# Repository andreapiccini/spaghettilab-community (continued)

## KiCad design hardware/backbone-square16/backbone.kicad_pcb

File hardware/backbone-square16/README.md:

# Backbone a 16 righe — variante separata

Stato: assegnazione GPIO e circuito a 16 porte applicati e verificati sulla netlist. PCB sincronizzato, disposizione preliminare 68 × 68 mm, non sbrogliato e non pronto per produzione. La Backbone originale non è stata sovrascritta.

Aprire `backbone.kicad_pro`. Il secondo foglio `ports16.kicad_sch` contiene i dieci canali aggiunti e i nuovi comandi. `gpio16-allocation.csv` è la tabella completa; `connectivity-checks.json` riporta le verifiche di collegamento.

## Righe configurabili

| Posizione | Sinistra: GPIO | Destra: GPIO |
|---|---:|---:|
| 1 | 7 | 12 |
| 2 | 8 | 15 |
| 3 | 9 | 16 |
| 4 | 10 | 38 |
| 5 | 1 | 39 |
| 6 | 2 | 40 |
| 7 | 6 | 41 |
| 8 | 11 | 42 |

Sinistra: J18/J19/J21, contatti 1–8, reti PORT_A0–PORT_A7. Destra: J22/J23/J24, contatti 1–8, reti PORT_A8–PORT_A15. Ogni riga ha tre contatti comuni. Le due metà sono indipendenti: nessuna matrice di collegamento fra righe.

Ogni riga dispone di selezione VCORE (3,3 V), GND, GPIO o alta impedenza mediante MOSFET e switch analogico. I GPIO non sono tolleranti a 5 V. Le nuove porte riprendono la topologia delle sei esistenti: shunt 0,1 Ω con prese Kelvin e collegamento 0 Ω rimovibile verso lo stadio di potenza. Il valore dello shunt non costituisce una specifica di corrente o di accuratezza già validata per la futura mezzanina.

L1–L7 hanno ADC1; L8 e R1–R3 hanno ADC2, con le limitazioni del relativo driver/modalità di acquisizione. R4–R8 non hanno ADC diretto. Tutti i 16 segnali restano GPIO reali del micro; gli expander comandano solo le selezioni e i servizi lenti.

## Funzioni conservate

| Funzione | GPIO conservati |
|---|---|
| I²C | 4, 5 |
| CAN | 17, 18 |
| USB | 19, 20 |
| LED RGB | 21 |
| Collegamento SPI e relativi segnali di controllo | 13, 14, 43, 44 |
| UART di programmazione AG32 | 47, 48 |

I GPIO 0, 3, 45 e 46 non sono assegnati alle righe; GPIO35–37 sono esclusi perché riservati alla PSRAM della variante ESP32 prevista. Gli eventuali collegamenti storici di questi segnali sulla vecchia interfaccia mezzanina non li rendono disponibili: andranno trattati come riservati nella revisione del connettore.

Le reti preesistenti dei servizi arrivano ancora ai rispettivi connettori. I comandi prima attestati ai dieci GPIO recuperati ora fanno capo agli expander. Il vecchio firmware non è compatibile con questa variante senza aggiornamento.

## Comandi aggiunti

Tre TCA9535 della famiglia già usata, U32/U33/U34, indirizzi I²C a 7 bit 0x21/0x22/0x23. U25 resta a 0x20. Gli indirizzi 0x20–0x23 devono essere riservati sulla rete I²C condivisa.

- U32: comandi P/N delle porte A6–A13, alternati su P00…P07 e P10…P17.
- U33: P/N delle porte A14–A15, dieci enable degli switch A6–A15 e ESP_ISO4_N/ESP_ISO5_N.
- U34: P00=MEAS_S0, P01=MEAS_S1, P02=MEAS_S2, P03=MEAS_INHIBIT, P04=EXT_SPI_CS_N, P05=ESP_AG_BOOT0, P06=ESP_AG_RESET_N, P07=MEZZ_PRESENT_N (ingresso). P10–P17 sono collegati a GND e devono restare ingressi.

La selezione EXT_SPI_CS_N ora richiede una transazione I²C: utilizzarla ai confini di una transazione SPI, mantenendola attiva durante il trasferimento. Non è più un chip-select commutabile direttamente a ogni parola tramite periferica ESP. Clock e dati del collegamento SPI conservano i GPIO diretti. Boot/reset dell'AG32 restano disponibili con il nuovo comando I²C.

## Contratto firmware da implementare

Gli expander partono come ingressi a freddo. Pull-up dei gate P e degli enable, e pull-down dei gate N, tengono disattivati i dieci nuovi stadi. Il reset del solo ESP32 non resetta gli expander: non garantisce il ritorno automatico in alta impedenza. Le sei porte esistenti conservano anche la loro logica di ownership.

Prima di rendere gli expander uscite, scrivere i latch nello stato sicuro. Per i nuovi componenti:

| Expander | Output port 0 | Output port 1 | Configuration port 0 | Configuration port 1 |
|---|---|---|---|---|
| U32 | 0x55 | 0x55 | 0x00 | 0x00 |
| U33 | 0xF5 | 0xFF | 0x00 | 0x00 |
| U34 | 0x58 | 0x00 | 0x80 | 0xFF |

Per U34 abilitare le uscite soltanto dopo aver assegnato l'ownership dei segnali condivisi: l'AG32 deve lasciare in alta impedenza i pin che l'expander pilota. In assenza di accordo lasciare i bit condivisi come ingressi. I selettori MEAS_S0–S2 hanno pull-down: non possono generare il livello alto con la sola emulazione open-drain. Occorre pilotaggio push-pull con un solo proprietario alla volta. Anche l'accesso I²C da due controllori richiede arbitraggio/ownership nel firmware.

Ogni cambio funzione deve passare da uno stato intermedio spento: disabilitare lo switch GPIO, spegnere entrambi i MOSFET, attendere l'assestamento, quindi abilitare una sola funzione. Non abilitare mai contemporaneamente P e N. Non alimentare una riga mentre ESP/FPGA o un dispositivo esterno la pilotano. Per ricevere/generare un segnale dalla futura mezzanina: P e N spenti, percorso ESP disabilitato, interfaccia esterna compatibile con tensioni e alimentazioni.

Questa tabella è una specifica di inizializzazione, non firmware già compilato o collaudato. Verificare limiti logici e stato di accensione anche con il modello esatto di expander acquistato e con la futura mezzanina collegata.

## Cosa resta per mezzanina e misure

La revisione del connettore è rinviata come concordato. Le sei porte storiche conservano i collegamenti esistenti. I dieci nuovi segnali e le venti nuove prese Kelvin non sono ancora esportati su J10/J11. Non è quindi ancora possibile usare tutte le 16 righe dall'FPGA della mezzanina attuale. Non sono stati aggiunti INA o DAC alla Backbone.

L'alta impedenza degli switch non elimina capacità parassite, leakage o collegamenti dello stadio di potenza: non è una garanzia di banda analogica. I link 0 Ω permettono di scollegare lo stadio di potenza per configurazioni dedicate; la banda va verificata con la mezzanina e il layout definitivo.

## Meccanica e controlli

PCB preliminare 68 × 68 mm, con magnetici ai lati e antenna ESP al bordo superiore. Tre socket per banco, interasse fra copie 5,08 mm, gap centrale 7,62 mm. Gli interassi delle prime sei posizioni fra J17/J18 e J20/J19 restano 33,02 mm. J10/J11 mantengono 24,175 mm tra centri; la posizione assoluta della mezzanina cambia e va verificata sul suo PCB. I nuovi componenti sono sul top; il modulo ESP/FlexyPin conserva il lato di montaggio originale.

La disposizione è una verifica preliminare di ingombro, non un layout ottimizzato e approvato per integrità di segnale, dissipazione o produzione. Sono ancora da qualificare l'inserimento dal bottom dei socket Hanxia, gli ingombri dei moduli e del case, la regione reale dell'antenna e gli accessi per manutenzione. Non è stato generato uno STEP completo del modulo ESP.

Il controllo della netlist verifica 16 GPIO distinti, 48 contatti di riga, collegamenti nuovi, preservazione delle funzioni e corrispondenza di 930 piazzole del PCB. Sono stati eliminati dalla copia i footprint duplicati e i due header campione fuori scheda. L'ERC mantiene avvisi dei simboli importati (pin non tipizzati) e delle prese di misura non ancora collegate. Il DRC non è pulito: rimangono soprattutto serigrafie, cinque sovrapposizioni dei courtyard dei socket a interasse fisso, anelli FlexyPin da qualificare e rame al bordo dei magnetici. Tutti i collegamenti sono ancora da sbrogliare. Vedere `erc.json` e `drc.json` per l'elenco completo, senza soppressione degli errori.

Il progetto di partenza conteneva soltanto la netclass Default: nella variante sono state ripristinate le 20 classi del controllo di sbroglio precedente ed estese alle nuove reti. Le larghezze sono impostazioni di progetto, non nuove certificazioni della corrente ammessa. Tutti i nuovi R/C usano 0603.

## Reversibilità

Questa cartella è una variante indipendente. Per tornare alla scheda precedente aprire il progetto originale `hardware/backbone/backbone.kicad_pro`. Nessun commit o push è stato eseguito per questa variante.

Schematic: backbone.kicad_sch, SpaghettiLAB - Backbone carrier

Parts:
C1: 100nF/50V; C0603; MPN CL10B104KB8NNNC; LCSC Part Name C1591
C5, C9, C86: 22uF; C_0603_1608Metric; MPN CL10A226MP8NUNE; LCSC Part C86295
C11: 1uF; C0603; LCSC Part Name C128624
C74, C88, C89: 100nF/50V; C0603; MPN CL10B104KB8NNNC; LCSC Part C1591
C84: 22pF; C_0603_1608Metric; MPN CL10C220JB8NNNC; LCSC Part C1653
C85: 100nF/50V; C_0603_1608Metric; MPN CL10B104KB8NNNC; LCSC Part C1591
C125, C126, C127, C128, C129, C130, C132, C133, C134, C135, C136, C137: 100nF/50V; C_0603_1608Metric; MPN CL10B104KB8NNNC; LCSC C1591
C139, C140: 10nF; C_0603_1608Metric; MPN CL10B103KB8NNNC; LCSC C1589
D6: SS54_C22452; SMA_L4.4-W2.8-LS5.4-R-RD; MPN SS54; LCSC Part C22452
D7: BAV70; SOT-23; MPN BAV70; LCSC C68978
H1, H2, H3, H4: MountingHole; MountingHole_2.2mm_M2_DIN965
J1, J140: M20-7810645R
J2: FROM_PREVIOUS; Magnetic_J2_Edge_DualFace
J3: M20-7810645R; DigiKey_Part_Number 952-M20-7810645RCT-ND
J4: SM04B-SRSS-TB(LF)(SN); JST_SH_SM04B-SRSS-TB_1x04-1MP_P1.00mm_Horizontal; MPN SM04B-SRSS-TB(LF)(SN); LCSC C160404
J9: TO NEXT; Magnetic_J9_Edge_DualFace
J10, J11: 61082-061402LF; CONN-SMD_61082-061402LF; LCSC C254696
J15, J16: A2541HWV-2x6P; CJT_A2541HWV-2x6P_P2.54mm_Vertical; MPN A2541HWV-2x6P; LCSC Part C239346
J17, J20: HX PM2.54-1x6P TP-YQ; Hanxia_C42380984_1x06_BottomAccess_Trial; MPN HX PM2.54-1x6P TP-YQ; LCSC C42380984
L1: 3.3uH; L_XRTC404012S; MPN XRTC404012S3R3MBCA; LCSC Part C39846848
LED1, LED2, LED3, LED4, LED5, LED6: SK6812MINI-E; LED_SK6812MINI-E_FR4_Window_HandFormed; MPN SK6812MINI-E; LCSC Part C5149201
Q2: AO3401A; SOT-23_L2.9-W1.3-P1.90-LS2.4-BR; MPN AO3401A; LCSC Part C15127
Q3, Q4, Q5, Q6, Q7, Q8: AO6604; SOT-23-6_L2.9-W1.6-P0.95-LS2.8-BL; MPN AO6604; LCSC C5182068
Q9: LMBT3946DW1T1G; SOT-363_SC-70-6; MPN LMBT3946DW1T1G; LCSC C136169
Q10: LMBT3904DW1T1G; SOT-363_SC-70-6; MPN LMBT3904DW1T1G; LCSC C131781
R4: 10k; R0603; MPN 0603WAF1002T5E; LCSC Part Name C25804
R5: 470R; R0603; MPN 0603WAF4700T5E; LCSC Part Name C23179
R8: 120R; R0603; MPN 0603WAF1200T5E; LCSC Part Name C2906988
R15, R16: 10k; R0603; MPN 0603WAF1002T5E; LCSC Part C25804
R17, R18: 33R; R0603; LCSC Part C2909394
R22, R27: 5.1k; R0603; LCSC Part C2907044
R24, R25: 4.7k; R0603
R36: 150k; R_0603_1608Metric; MPN 0603WAF1503T5E; LCSC Part C22807
R37: 33.2k; R_0603_1608Metric; MPN 0603WAF3322T5E; LCSC Part C23003
R38, R39, R40, R41, R42, R43, R44, R45, R46, R47, R48, R49, R50, R51, R52, R53, R54, R55: 100k; R0603
R56, R57, R58, R59, R60, R61: 0.1R; R_0603_2Terminal_Kelvin; MPN PE0603FRF070R1L; LCSC C1882650
R103, R105, R124, R127, R129, R132: 100k; R_0603_1608Metric; MPN 0603WAF1003T5E; LCSC C25803
R104: 47k; R_0603_1608Metric; MPN 0603WAF4702T5E; LCSC C25819
R110, R111, R115: 100k; R_0603_1608Metric; LCSC C25803
R112, R113, R114: 0R; R_0603_1608Metric; LCSC C21189; not fitted
R117, R118, R119, R120, R121, R122: 0R; R_0603_1608Metric; MPN RC0603JR-070RL; LCSC C95177
R123, R125, R126, R130: 10k; R_0603_1608Metric; MPN 0603WAF1002T5E; LCSC C25804
R128, R131: 22k; R_0603_1608Metric; MPN 0603WAF2202T5E; LCSC C31850
TP15: SMD/0.6mm; TestPoint_Pad_D1.0mm
U1: ESP32-S3-WROOM-1_1U_FlexyPin_Socket
U2: SN65HVD230DR; SOIC-8_L4.9-W3.9-P1.27-LS6.0-BL; MPN SN65HVD230DR; LCSC Part C12084
U3: HC-TYPE-C-16P-01A; USB-C-SMD_HC-TYPE-C-16P-01A; MPN HC-TYPE-C-16P-01A; LCSC Part C2894897
U4: SY8089AAAC; SOT-23-5; MPN SY8089AAAC; LCSC Part C78988
U8: G3VM-61VY3; SMD-4_L4.6-W3.7-P2.54-LS7.0-TL; MPN G3VM-61VY3(TR); LCSC Part C2152318
U12, U13: SN74CBTLV3125PWR; TSSOP-14_L5.0-W4.4-P0.65-LS6.4-BL; LCSC C406866
U25: TCA9535PWR(UMW); TSSOP-24_L7.8-W4.4-P0.65-LS6.4-BL; LCSC C22396388
U26, U27, U28, U29: SN74LVC1G3157DCKR; SOT-363_SC-70-6; LCSC C38663
U31: TS3USB221ARSER; UQFN-10_L2.0-W1.5-P0.50-BL; LCSC C128396

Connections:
5V: C5.1, C85.1, C140.1, D6.2 (K), J2.1, J9.1, J10.1, J10.2, J10.5, J11.1, J11.2, J11.5, Q2.2 (S), Q9.4 (E), R4.1, R125.1, R127.1, R130.1, U4.1 (EN), U4.4 (IN)
/BUCK_FB: C84.2, R36.2, R37.1, U4.5 (FB)
/BUCK_SW: L1.1, U4.3 (LX)
/LED_CHAIN_1: LED1.4 (DOUT), LED2.2 (DIN)
/LED_CHAIN_2: LED2.4 (DOUT), LED3.2 (DIN)
/LED_CHAIN_3: LED3.4 (DOUT), LED4.2 (DIN)
/LED_CHAIN_4: LED4.4 (DOUT), LED5.2 (DIN)
/LED_CHAIN_5: LED5.4 (DOUT), LED6.2 (DIN)
/PWR_DRV_A0: Q3.4 (D), Q3.6 (D), R117.1
/PWR_DRV_A1: Q4.4 (D), Q4.6 (D), R118.1
/PWR_DRV_A2: Q5.4 (D), Q5.6 (D), R119.1
/PWR_DRV_A3: Q6.4 (D), Q6.6 (D), R120.1
/PWR_DRV_A4: Q7.4 (D), Q7.6 (D), R121.1
/PWR_DRV_A5: Q8.4 (D), Q8.6 (D), R122.1
/TERM_DRIVE: Q2.3 (D), R5.2
/TERM_LED: R5.1, U8.1
/TERM_R: R8.2, U8.3
/USB_CC1: R22.1, U3.A5 (CC1)
/USB_CC2: R27.2, U3.B5 (CC2)
A0: J3.7, J10.6, J17.3, U1.7 (IO7), U12.2 (A)
A1: J3.1, J10.9, J17.4, U1.12 (IO8), U12.5 (A)
A2: J3.12, J10.13, J17.5, U1.17 (IO9), U12.9 (A)
A3: J3.10, J10.17, J17.6, U1.18 (IO10), U12.12 (A)
A4: J3.8, J10.21, J20.1, U1.39 (IO1), U13.2 (A)
A5: J3.6, J10.24, J20.4, U1.38 (IO2), U13.5 (A)
A6: U1.6 (IO6), U13.9 (A)
A7: U1.19 (IO11), U13.12 (A)
A8: U1.20 (IO12); also elsewhere on the board
A9: U1.8 (IO15); also elsewhere on the board
A10: U1.9 (IO16); also elsewhere on the board
A11: U1.31 (IO38); also elsewhere on the board
A12: U1.32 (IO39); also elsewhere on the board
A13: U1.33 (IO40); also elsewhere on the board
A14: U1.34 (IO41); also elsewhere on the board
A15: U1.35 (IO42); also elsewhere on the board
AG_CAN_TX: J10.34, U26.1 (B2_AG)
AG_ISO4_N: J10.36, U28.1 (B2_AG)
AG_ISO5_N: J10.37, U29.1 (B2_AG)
AG_LED_DATA: J10.38, U27.1 (B2_AG)
ALED: LED1.2 (DIN), R105.1, U27.4 (A_OUT)
BOOT: J10.28, R15.2, U1.27 (IO0)
CAN_H: J2.2, J9.2, J11.46, R8.1, U2.7 (CANH)
CAN_L: J2.3, J9.3, J11.47, U2.6 (CANL), U8.4
CAN_RX: J10.39, U1.11 (IO18), U2.4 (R)
CAN_TX: R104.2, U2.1 (D), U26.4 (A_OUT)
CTRL13: J10.41, U1.21 (IO13)
CTRL14: J10.42, U1.22 (IO14)
ESP35_AUX: J10.43, R112.2
ESP36_AUX: J10.44, R113.2
ESP37_AUX: J10.46, R114.2
ESP_AG_BOOT0: J10.29; also elsewhere on the board
ESP_AG_RESET_N: J10.31; also elsewhere on the board
ESP_CAN_TX: J10.47, U1.10 (IO17), U26.3 (B1_ESP)
ESP_ISO4_N: J10.48, U28.3 (B1_ESP); also elsewhere on the board
ESP_ISO5_N: J10.49, U29.3 (B1_ESP); also elsewhere on the board
ESP_LED_DATA: J10.51, U1.23 (IO21), U27.3 (B1_ESP)
ESP_PROG_RX: J10.32, U1.25 (IO48)
ESP_PROG_TX: J10.33, U1.24 (IO47)
EXT_SPI_CS_N: J10.52; also elsewhere on the board
GND: C1.2, C5.2, C9.2, C11.1, C74.1, C85.2, C86.2, C88.2, C89.2, C125.2, C126.2, C127.2, C128.2, C129.2, C130.2, C132.2, C133.2, C134.2, C135.2, C136.2, C137.2, C139.2, J2.5, J3.4, J3.5, J3.9, J4.1 (GND), J9.5, J10.15, J10.20, J10.25, J10.30, J10.35, J10.40, J10.45, J10.50, J10.55, J11.15, J11.20, J11.25, J11.30, J11.35, J11.40, J11.45, J11.50, J17.1, J20.2, J20.6, LED1.1 (GND), LED2.1 (GND), LED3.1 (GND), LED4.1 (GND), LED5.1 (GND), LED6.1 (GND), Q3.5 (S), Q4.5 (S), Q5.5 (S), Q6.5 (S), Q7.5 (S), Q8.5 (S), Q9.1 (E), Q10.1 (E), Q10.4 (E), R22.2, R27.1, R37.2, R39.2, R41.2, R43.2, R45.2, R47.2, R49.2, R103.2, R105.2, R111.2, R124.2, R129.2, R132.2, U1.1 (GND), U1.40 (GND), U2.2 (GND), U2.8 (RS), U3.1 (SHELL), U3.2 (SHELL), U3.3 (SHELL), U3.4 (SHELL), U3.A1B12 (GND), U3.B1A12 (GND), U4.2 (GND), U8.2, U12.7 (GND), U13.7 (GND), U25.2 (A1), U25.3 (A2), U25.12 (GND), U25.21 (A0), U26.2 (GND), U27.2 (GND), U28.2 (GND), U29.2 (GND), U31.5 (GND), U31.6 (OE_N); also elsewhere on the board
IO3: J10.53, U1.15 (IO3)
IO4: J4.3 (SDA), J10.54, R24.2, U1.4 (IO4), U25.23 (SDA); also elsewhere on the board
IO5: J4.4 (SCL), J11.7, R25.2, U1.5 (IO5), U25.22 (SCL); also elsewhere on the board
IO35: R112.1, U1.28 (IO35)
IO36: R113.1, U1.29 (IO36)
IO37: R114.1, U1.30 (IO37)
IO45: J10.56, U1.26 (IO45)
IO46: J11.6, U1.16 (IO46)
ISO_A0_N: J11.41, R50.2, U12.1 (~OE), U25.17 (P14)
ISO_A1_N: J11.42, R51.2, U12.4 (~OE), U25.18 (P15)
ISO_A2_N: J11.43, R52.2, U12.10 (~OE), U25.19 (P16)
ISO_A3_N: J11.44, R53.2, U12.13 (~OE), U25.20 (P17)
ISO_A4_N: J11.8, R54.2, U13.1 (~OE), U28.4 (A_OUT)
ISO_A5_N: J11.9, R55.2, U13.4 (~OE), U29.4 (A_OUT)
ISO_A6_N: U13.10 (~OE); also elsewhere on the board
ISO_A7_N: U13.13 (~OE); also elsewhere on the board
LED_EXP_DATA: J11.52, LED6.4 (DOUT)
MEAS_INHIBIT: J11.11; also elsewhere on the board
MEAS_S0: J11.12; also elsewhere on the board
MEAS_S1: J11.13; also elsewhere on the board
MEAS_S2: J11.14; also elsewhere on the board
MEZZ_OWNER: J11.16, R103.1, U26.6 (S_AG_READY), U27.6 (S_AG_READY), U28.6 (S_AG_READY), U29.6 (S_AG_READY), U31.9 (S_MEZZ)
MEZZ_PRESENT_N: J11.17, R115.2; also elsewhere on the board
N_A0: J10.7, R56.1, R117.2, U12.3 (B)
N_A1: J10.11, R57.1, R118.2, U12.6 (B)
N_A2: J10.14, R58.1, R119.2, U12.8 (B)
N_A3: J10.18, R59.1, R120.2, U12.11 (B)
N_A4: J10.22, R60.1, R121.2, U13.3 (B)
N_A5: J10.26, R61.1, R122.2, U13.6 (B)
N_A6: U13.8 (B); also elsewhere on the board
N_A7: U13.11 (B); also elsewhere on the board
N_GATE_0: J11.27, Q3.1 (G), R39.1, U25.5 (P01)
N_GATE_1: J11.29, Q4.1 (G), R41.1, U25.7 (P03)
N_GATE_2: J11.32, Q5.1 (G), R43.1, U25.9 (P05)
N_GATE_3: J11.34, Q6.1 (G), R45.1, U25.11 (P07)
N_GATE_4: J11.37, Q7.1 (G), R47.1, U25.14 (P11)
N_GATE_5: J11.39, Q8.1 (G), R49.1, U25.16 (P13)
PORT_A0: J1.1, J1.2, J10.8, J140.1, J140.2, R56.2; also elsewhere on the board
PORT_A1: J1.3, J1.4, J10.12, J140.3, J140.4, R57.2; also elsewhere on the board
PORT_A2: J1.5, J1.6, J10.16, J140.5, J140.6, R58.2; also elsewhere on the board
PORT_A3: J1.7, J1.8, J10.19, J140.7, J140.8, R59.2; also elsewhere on the board
PORT_A4: J1.9, J1.10, J10.23, J140.9, J140.10, R60.2; also elsewhere on the board
PORT_A5: J1.11, J1.12, J10.27, J140.11, J140.12, R61.2; also elsewhere on the board
P_GATE_0: J11.26, Q3.3 (G), R38.2, U25.4 (P00)
P_GATE_1: J11.28, Q4.3 (G), R40.2, U25.6 (P02)
P_GATE_2: J11.31, Q5.3 (G), R42.2, U25.8 (P04)
P_GATE_3: J11.33, Q6.3 (G), R44.2, U25.10 (P06)
P_GATE_4: J11.36, Q7.3 (G), R46.2, U25.13 (P10)
P_GATE_5: J11.38, Q8.3 (G), R48.2, U25.15 (P12)
SHUNT_SENSE_H0: J10.57, R56.3
SHUNT_SENSE_H1: J10.59, R57.3
SHUNT_SENSE_H2: J11.53, R58.3
SHUNT_SENSE_H3: J11.55, R59.3
SHUNT_SENSE_H4: J11.57, R60.3
SHUNT_SENSE_H5: J11.59, R61.3
SHUNT_SENSE_L0: J10.58, R56.4
SHUNT_SENSE_L1: J10.60, R57.4
SHUNT_SENSE_L2: J11.54, R58.4
SHUNT_SENSE_L3: J11.56, R59.4
SHUNT_SENSE_L4: J11.58, R60.4
SHUNT_SENSE_L5: J11.60, R61.4
SPI_MISO: J11.18, U1.36 (RXD0)
SPI_MOSI: J11.19, U1.37 (TXD0)
TERM_ABSENT_L: D7.1 (A), Q9.6 (C), R125.2
TERM_ABSENT_OR: D7.3 (K), R131.1
TERM_ABSENT_R: D7.2 (A), Q10.6 (C), R130.2
TERM_BASE_DRIVE: Q10.5 (B), R131.2, R132.1
TERM_BASE_INV: Q10.2 (B), R128.2, R129.1
TERM_BASE_L: C139.1, Q9.2 (B), R123.2, R124.1
TERM_BASE_R: C140.2, Q9.5 (B), R126.2, R127.2
TERM_CTRL_IN: J2.4, J11.48, R123.1
TERM_CTRL_OUT: J9.4, J11.49, R126.1
TERM_GATE_N: Q2.1 (G), Q10.3 (C), R4.2
TERM_PRESENT_R: Q9.3 (C), R128.1
USB_D+: U3.A6 (D+), U3.B6 (D+), U31.8 (USB_D+)
USB_D-: U3.A7 (D-), U3.B7 (D-), U31.7 (USB_D-)
USB_ESP_D+: R17.2, U1.14 (USB_D+)
USB_ESP_D-: R18.2, U1.13 (USB_D-)
USB_SW_AG_N: J11.21, U31.4 (AG_D-)
USB_SW_AG_P: J11.22, U31.3 (AG_D+)
USB_SW_ESP_N: R18.1, U31.2 (ESP_D-)
USB_SW_ESP_P: R17.1, U31.1 (ESP_D+)
USB_VBUS_SENSE: J11.23, R110.2, R111.1
VBUS: D6.1 (A), J11.51, R110.1, U3.A4B9 (VBUS), U3.B4A9 (VBUS)
VCORE: C1.1, C9.1, C74.2, C84.1, C86.1, C88.1, C89.1, C125.1, C126.1, C127.1, C128.1, C129.1, C130.1, C132.1, C133.1, C134.1, C135.1, C136.1, C137.1, J3.2, J3.3, J3.11, J4.2 (+3V3), J10.3, J10.4, J10.10, J11.3, J11.4, J11.10, J17.2, J20.3, J20.5, L1.2, LED1.3 (VDD), LED2.3 (VDD), LED3.3 (VDD), LED4.3 (VDD), LED5.3 (VDD), LED6.3 (VDD), Q3.2 (S), Q4.2 (S), Q5.2 (S), Q6.2 (S), Q7.2 (S), Q8.2 (S), R15.1, R16.1, R24.1, R25.1, R36.1, R38.1, R40.1, R42.1, R44.1, R46.1, R48.1, R50.1, R51.1, R52.1, R53.1, R54.1, R55.1, R104.1, R115.1, TP15.1 (1_1), U1.2 (3V3), U2.3 (VCC), U12.14 (VCC), U13.14 (VCC), U25.24 (VCC), U26.5 (VCC), U27.5 (VCC), U28.5 (VCC), U29.5 (VCC), U31.10 (VCC); also elsewhere on the board
~RESET: C11.2, J11.24, R16.2, U1.3 (EN)

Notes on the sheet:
J3 | DIRECT ESP32 ACCESS
is USB voltage, not 3.3 V logic.
U1 | OPTIONAL ESP32-S3
U26-U29 | AUTOMATIC CONTROLLER SELECTION
U25 | PORT CONFIGURATION
Bottom insertion | 20.72 x 5 x 5 mm | land pattern requires physical qualification
USB-C + U31 | COMPUTER CONNECTION
Powers the carrier and the removable Expansion module.
Connects compatible sensors through a four-wire cable.
J4 | QWIIC SENSOR LINK
P1-P6 = external experiment rows | A0-A5 = ESP-side signals | J3 = separate direct access. Named arrows connect blocks.
U2 | CAN TRANSCEIVER
Adds Wi-Fi, Bluetooth and familiar ESP32 development tools.
LED1-LED6 | PORT STATUS
Six configurable ports. Header and serial LED order: P1-P6.
Gives Expansion priority; the base uses ESP32 when no module is fitted.
Unconnected mechanical samples. Not fitted in production.
READING GUIDE: Q3-Q8 = power stages | U12/U13 = signal isolation | J1/J140 = shared headers | R56-R61 = shunts
INTERFACE V3: 120/120 assigned | 17 GND | 6 x 5V | 6 x VCORE | 12 dedicated shunt sense | all services retained.
Passes power and messages between neighbouring backbones.
Physical IC groups | all units of each IC together | named nets preserve functional links
GPIO35/36/37 AUX links are DNP PSRAM guards. Fit only on compatible ESP32 variants. USB does not pass through FPGA logic.
Q9/Q10 detect both neighbours by TERM current. Q2/U8 insert 120R at either end. No MCU.
2 x 6 contacts | 2.54 mm pitch | body 15.74 x 5.00 x 8.50 mm
MEZZ_OWNER LOW = ESP32, HIGH = Expansion. R103 = 100k pull-down; Expansion adds R109 = 10k pull-up. Claim is not firmware-ready. USB, CAN TX, RGB and ISO4/5 are selected.
CJT CONNECTOR FIT TEST | J15 / J16
J2 / J9 | MAGNETIC CAN LINK
U31: LOW selects ESP32, HIGH selects Expansion. Both USB series-resistor pairs are fitted. Owner changes require USB detach and re-enumeration.
Shared I2C control of the six power stages.
Added gate / ISO signals are shared with U25: release its outputs before external drive. VBUS
Provides fixed ESP32, supply and ground connections.
Connects USB to the selected controller.
J17 / J20: direct ESP sensor rows, A0-A5 plus mixed 3V3 / GND. J18 / J19: configurable P1-P6.
SPAGHETTILAB | BACKBONE CARRIER
U4 | 5 V TO 3.3 V SUPPLY
J10 / J11 | EXPANSION INTERFACE - 2 x 60 CONTACTS
BKL 2x8 DUAL ENTRY | SENSOR & CONFIGURABLE HEADERS
Turns controller messages into CAN bus signals.
U25 + C129: common to all variants. One active I2C master at a time. U12/U13 are grouped separately below.
P1 | Q3 POWER STAGE

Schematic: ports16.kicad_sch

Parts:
C141, C142, C143, C144, C145: 100nF/50V; C0603; MPN CL10B104KB8NNNC; LCSC Part C1591
J18, J19, J21, J22, J23, J24: HX PM2.54-1x8P TP-YQ; Hanxia_C42380985_1x08_BottomAccess_Trial; MPN HX PM2.54-1x6P TP-YQ; LCSC C42380985
Q11, Q12, Q13, Q14, Q15, Q16, Q17, Q18, Q19, Q20: AO6604; SOT-23-6_L2.9-W1.6-P0.95-LS2.8-BL; MPN AO6604; LCSC C5182068
R133, R134, R135, R136, R137, R138, R139, R140, R141, R142: 0.1R; R_0603_2Terminal_Kelvin; MPN PE0603FRF070R1L; LCSC C1882650
R143, R144, R145, R146, R147, R148, R149, R150, R151, R152, R153, R154, R155, R156, R157, R158, R159, R160, R161, R162, R163, R164, R165, R166, R167, R168, R169, R170, R171, R172, R183, R184, R185, R186, R187, R188, R189: 100k; R0603
R173, R174, R175, R176, R177, R178, R179, R180, R181, R182: 0R; R_0603_1608Metric; MPN RC0603JR-070RL; LCSC C95177
U32, U33, U34: TCA9535PWR(UMW); TSSOP-24_L7.8-W4.4-P0.65-LS6.4-BL; LCSC C22396388
U35, U36: SN74CBTLV3125PWR; TSSOP-14_L5.0-W4.4-P0.65-LS6.4-BL; LCSC C406866

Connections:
A8: U35.2 (A); also elsewhere on the board
A9: U35.5 (A); also elsewhere on the board
A10: U35.9 (A); also elsewhere on the board
A11: U35.12 (A); also elsewhere on the board
A12: U36.2 (A); also elsewhere on the board
A13: U36.5 (A); also elsewhere on the board
A14: U36.9 (A); also elsewhere on the board
A15: U36.12 (A); also elsewhere on the board
DRIVER_A6: Q11.4 (D), Q11.6 (D), R173.1
DRIVER_A7: Q12.4 (D), Q12.6 (D), R174.1
DRIVER_A8: Q13.4 (D), Q13.6 (D), R175.1
DRIVER_A9: Q14.4 (D), Q14.6 (D), R176.1
DRIVER_A10: Q15.4 (D), Q15.6 (D), R177.1
DRIVER_A11: Q16.4 (D), Q16.6 (D), R178.1
DRIVER_A12: Q17.4 (D), Q17.6 (D), R179.1
DRIVER_A13: Q18.4 (D), Q18.6 (D), R180.1
DRIVER_A14: Q19.4 (D), Q19.6 (D), R181.1
DRIVER_A15: Q20.4 (D), Q20.6 (D), R182.1
ESP_AG_BOOT0: R188.2, U34.9 (P05); also elsewhere on the board
ESP_AG_RESET_N: R189.2, U34.10 (P06); also elsewhere on the board
ESP_ISO4_N: U33.19 (P16); also elsewhere on the board
ESP_ISO5_N: U33.20 (P17); also elsewhere on the board
EXT_SPI_CS_N: R187.2, U34.8 (P04); also elsewhere on the board
GND: C141.2, C142.2, C143.2, C144.2, C145.2, Q11.5 (S), Q12.5 (S), Q13.5 (S), Q14.5 (S), Q15.5 (S), Q16.5 (S), Q17.5 (S), Q18.5 (S), Q19.5 (S), Q20.5 (S), R144.2, R146.2, R148.2, R150.2, R152.2, R154.2, R156.2, R158.2, R160.2, R162.2, R183.1, R184.1, R185.1, R188.1, U32.2 (A1), U32.3 (A2), U32.12 (GND), U33.3 (A2), U33.12 (GND), U33.21 (A0), U34.3 (A2), U34.12 (GND), U34.13 (P10), U34.14 (P11), U34.15 (P12), U34.16 (P13), U34.17 (P14), U34.18 (P15), U34.19 (P16), U34.20 (P17), U35.7 (GND), U36.7 (GND); also elsewhere on the board
IO4: U32.23 (SDA), U33.23 (SDA), U34.23 (SDA); also elsewhere on the board
IO5: U32.22 (SCL), U33.22 (SCL), U34.22 (SCL); also elsewhere on the board
ISO_A6_N: R163.2, U33.8 (P04); also elsewhere on the board
ISO_A7_N: R164.2, U33.9 (P05); also elsewhere on the board
ISO_A8_N: R165.2, U33.10 (P06), U35.1 (~OE)
ISO_A9_N: R166.2, U33.11 (P07), U35.4 (~OE)
ISO_A10_N: R167.2, U33.13 (P10), U35.10 (~OE)
ISO_A11_N: R168.2, U33.14 (P11), U35.13 (~OE)
ISO_A12_N: R169.2, U33.15 (P12), U36.1 (~OE)
ISO_A13_N: R170.2, U33.16 (P13), U36.4 (~OE)
ISO_A14_N: R171.2, U33.17 (P14), U36.10 (~OE)
ISO_A15_N: R172.2, U33.18 (P15), U36.13 (~OE)
MEAS_INHIBIT: R186.2, U34.7 (P03); also elsewhere on the board
MEAS_S0: R183.2, U34.4 (P00); also elsewhere on the board
MEAS_S1: R184.2, U34.5 (P01); also elsewhere on the board
MEAS_S2: R185.2, U34.6 (P02); also elsewhere on the board
MEZZ_PRESENT_N: U34.11 (P07); also elsewhere on the board
N_A6: R133.1, R173.2; also elsewhere on the board
N_A7: R134.1, R174.2; also elsewhere on the board
N_A8: R135.1, R175.2, U35.3 (B)
N_A9: R136.1, R176.2, U35.6 (B)
N_A10: R137.1, R177.2, U35.8 (B)
N_A11: R138.1, R178.2, U35.11 (B)
N_A12: R139.1, R179.2, U36.3 (B)
N_A13: R140.1, R180.2, U36.6 (B)
N_A14: R141.1, R181.2, U36.8 (B)
N_A15: R142.1, R182.2, U36.11 (B)
N_GATE_6: Q11.1 (G), R144.1, U32.5 (P01)
N_GATE_7: Q12.1 (G), R146.1, U32.7 (P03)
N_GATE_8: Q13.1 (G), R148.1, U32.9 (P05)
N_GATE_9: Q14.1 (G), R150.1, U32.11 (P07)
N_GATE_10: Q15.1 (G), R152.1, U32.14 (P11)
N_GATE_11: Q16.1 (G), R154.1, U32.16 (P13)
N_GATE_12: Q17.1 (G), R156.1, U32.18 (P15)
N_GATE_13: Q18.1 (G), R158.1, U32.20 (P17)
N_GATE_14: Q19.1 (G), R160.1, U33.5 (P01)
N_GATE_15: Q20.1 (G), R162.1, U33.7 (P03)
PORT_A0: J18.1, J19.1, J21.1; also elsewhere on the board
PORT_A1: J18.2, J19.2, J21.2; also elsewhere on the board
PORT_A2: J18.3, J19.3, J21.3; also elsewhere on the board
PORT_A3: J18.4, J19.4, J21.4; also elsewhere on the board
PORT_A4: J18.5, J19.5, J21.5; also elsewhere on the board
PORT_A5: J18.6, J19.6, J21.6; also elsewhere on the board
PORT_A6: J18.7, J19.7, J21.7, R133.2
PORT_A7: J18.8, J19.8, J21.8, R134.2
PORT_A8: J22.1, J23.1, J24.1, R135.2
PORT_A9: J22.2, J23.2, J24.2, R136.2
PORT_A10: J22.3, J23.3, J24.3, R137.2
PORT_A11: J22.4, J23.4, J24.4, R138.2
PORT_A12: J22.5, J23.5, J24.5, R139.2
PORT_A13: J22.6, J23.6, J24.6, R140.2
PORT_A14: J22.7, J23.7, J24.7, R141.2
PORT_A15: J22.8, J23.8, J24.8, R142.2
P_GATE_6: Q11.3 (G), R143.2, U32.4 (P00)
P_GATE_7: Q12.3 (G), R145.2, U32.6 (P02)
P_GATE_8: Q13.3 (G), R147.2, U32.8 (P04)
P_GATE_9: Q14.3 (G), R149.2, U32.10 (P06)
P_GATE_10: Q15.3 (G), R151.2, U32.13 (P10)
P_GATE_11: Q16.3 (G), R153.2, U32.15 (P12)
P_GATE_12: Q17.3 (G), R155.2, U32.17 (P14)
P_GATE_13: Q18.3 (G), R157.2, U32.19 (P16)
P_GATE_14: Q19.3 (G), R159.2, U33.4 (P00)
P_GATE_15: Q20.3 (G), R161.2, U33.6 (P02)
SHUNT_SENSE_H6: R133.3
SHUNT_SENSE_H7: R134.3
SHUNT_SENSE_H8: R135.3
SHUNT_SENSE_H9: R136.3
SHUNT_SENSE_H10: R137.3
SHUNT_SENSE_H11: R138.3
SHUNT_SENSE_H12: R139.3
SHUNT_SENSE_H13: R140.3
SHUNT_SENSE_H14: R141.3
SHUNT_SENSE_H15: R142.3
SHUNT_SENSE_L6: R133.4
SHUNT_SENSE_L7: R134.4
SHUNT_SENSE_L8: R135.4
SHUNT_SENSE_L9: R136.4
SHUNT_SENSE_L10: R137.4
SHUNT_SENSE_L11: R138.4
SHUNT_SENSE_L12: R139.4
SHUNT_SENSE_L13: R140.4
SHUNT_SENSE_L14: R141.4
SHUNT_SENSE_L15: R142.4
VCORE: C141.1, C142.1, C143.1, C144.1, C145.1, Q11.2 (S), Q12.2 (S), Q13.2 (S), Q14.2 (S), Q15.2 (S), Q16.2 (S), Q17.2 (S), Q18.2 (S), Q19.2 (S), Q20.2 (S), R143.1, R145.1, R147.1, R149.1, R151.1, R153.1, R155.1, R157.1, R159.1, R161.1, R163.1, R164.1, R165.1, R166.1, R167.1, R168.1, R169.1, R170.1, R171.1, R172.1, R186.1, R187.1, R189.1, U32.21 (A0), U32.24 (VCC), U33.2 (A1), U33.24 (VCC), U34.2 (A1), U34.21 (A0), U34.24 (VCC), U35.14 (VCC), U36.14 (VCC); also elsewhere on the board

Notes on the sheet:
U32: I2C 0x21 / port controls
U33: I2C 0x22 / port controls
U34: I2C 0x23 / slow services; presence input
PORT 7 / L7 / GPIO6
GPIO switch: U13C on main sheet
PORT 8 / L8 / GPIO11
GPIO switch: U13D on main sheet
PORT 9 / R1 / GPIO12
PORT 10 / R2 / GPIO15
PORT 11 / R3 / GPIO16
PORT 12 / R4 / GPIO38
PORT 13 / R5 / GPIO39
PORT 14 / R6 / GPIO40
PORT 15 / R7 / GPIO41
PORT 16 / R8 / GPIO42
LEFT L1-L8 / 3 contacts per independent node
RIGHT R1-R8 / 3 contacts per independent node
VCORE = 3.3 V. Disable GPIO path before selecting a rail. Never enable both MOSFETs. No crosspoint matrix. Firmware and mezzanine interface revision required. Existing six shunts retained; ten added sense pairs are local only until the interface is redesigned.

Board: 4 copper layers, 212 parts (1 on the bottom side), 202 nets, no tracks yet.

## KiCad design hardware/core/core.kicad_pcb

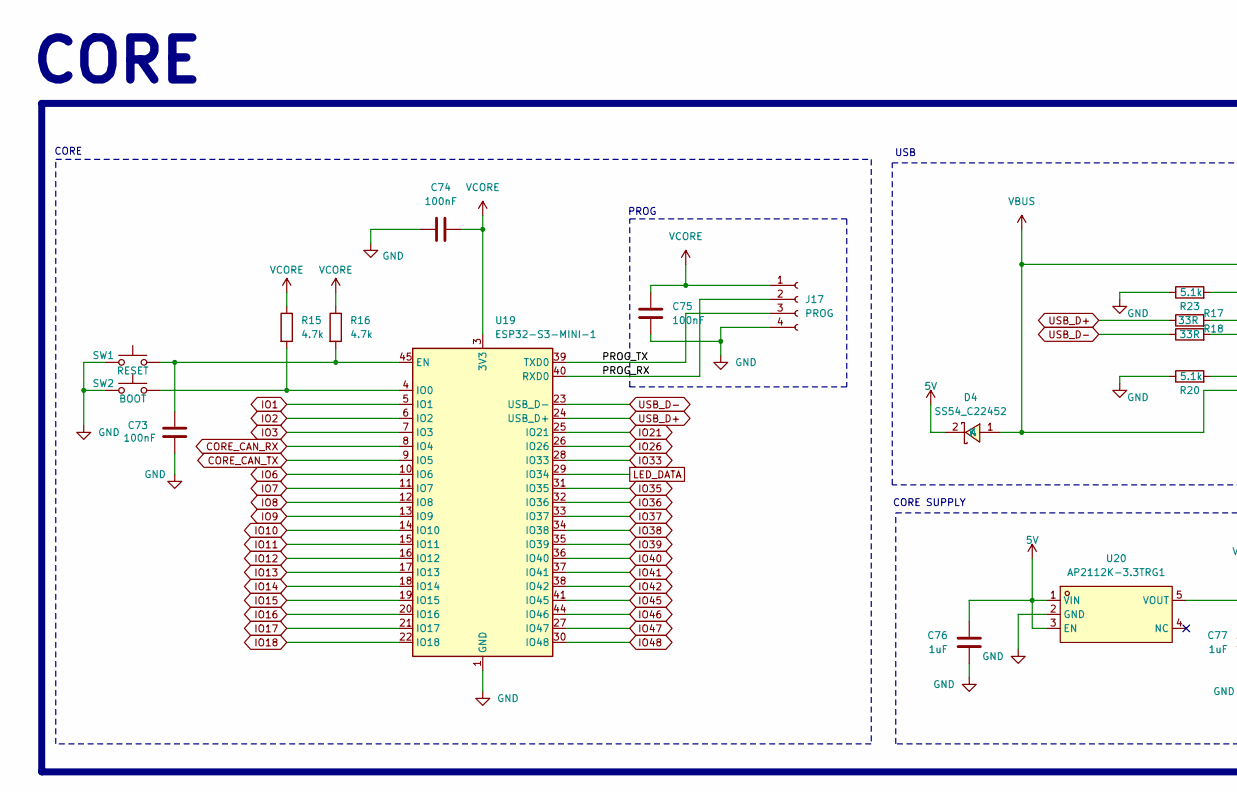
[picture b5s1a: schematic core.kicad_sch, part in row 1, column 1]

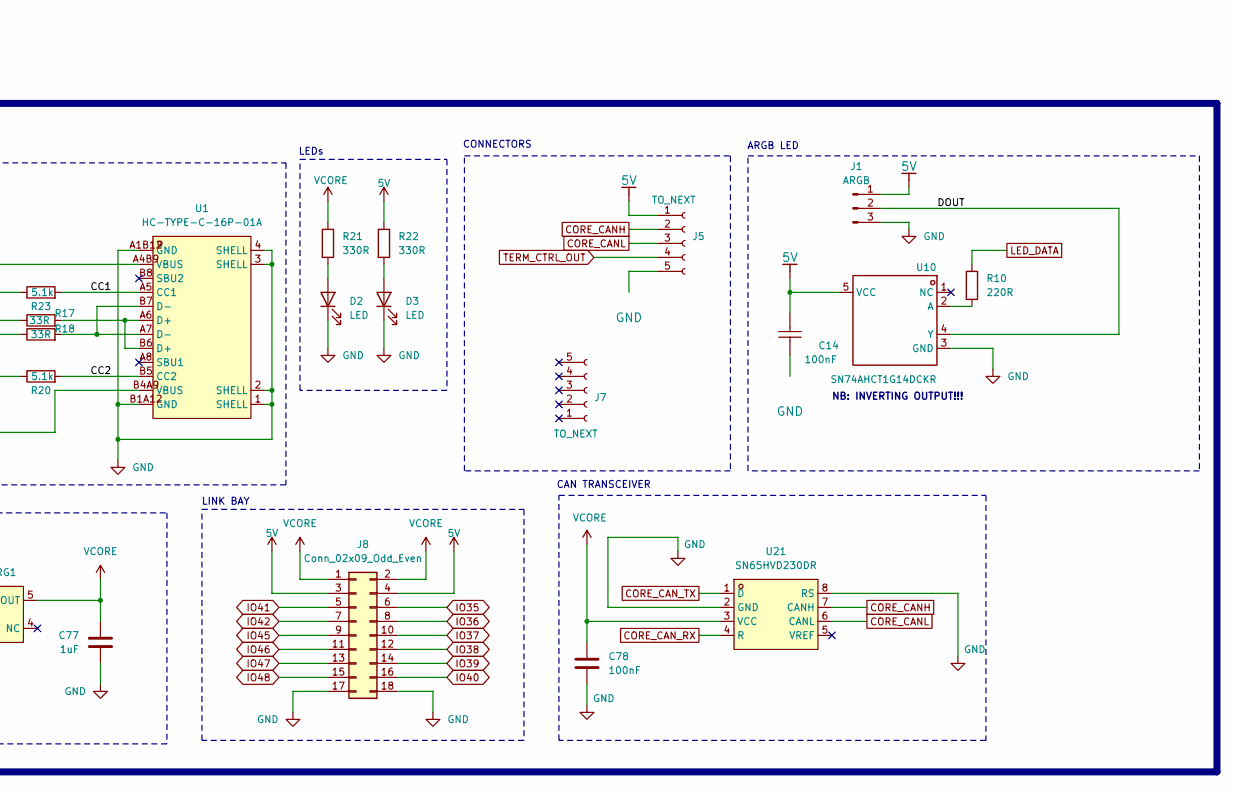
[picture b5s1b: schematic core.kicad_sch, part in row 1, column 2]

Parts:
C14, C73, C74, C75: 100nF; C0603; LCSC Part C1591
C76, C77: 1uF; C0603; LCSC Part C128624
C78: 100nF; C0603; MPN CL05B104KA5NNNC; LCSC Part C1591
D2, D3: LED; LED0603-RD; LCSC Part C19273150
D4: SS54_C22452; SMA_L4.4-W2.8-LS5.4-R-RD; MPN SS54; LCSC Part C22452
J1: ARGB; PinHeader_1x03_P2.54mm_Vertical
J5, J7: TO_NEXT; PinSocket_1x05_P2.54mm_Horizontal
J8: Conn_02x09_Odd_Even; PinSocket_2x09_P2.54mm_Horizontal
J17: PROG; PinSocket_1x04_P2.54mm_Vertical
R10: 220R; R0603; LCSC Part C22962
R15, R16: 4.7k; R0603; LCSC Part C99782
R17, R18: 33R; R0603; LCSC Part C2909394
R20, R23: 5.1k; R0603; LCSC Part C2907044
R21, R22: 330R; R0603; LCSC Part C105881
SW1: RESET; SW-SMD_4P-L5.1-W5.1-P3.70-LS6.5-TL_H1.5; LCSC Part C318884
SW2: BOOT; SW-SMD_4P-L5.1-W5.1-P3.70-LS6.5-TL_H1.5; LCSC Part C318884
U1: HC-TYPE-C-16P-01A; USB-C-SMD_HC-TYPE-C-16P-01A; MPN HC-TYPE-C-16P-01A; LCSC Part C2894897
U10: SN74AHCT1G14DCKR; SOT-353_L2.2-W1.4-P0.65-LS2.4-BR; Manufacturer Part SN74AHCT1G14DCKR; LCSC Part Name 单路施密特触发反相器
U19: ESP32-S3-MINI-1; ESP32-S2-MINI-1; LCSC Part C2913206
U20: AP2112K-3.3TRG1; SOT-25-5_L2.9-W1.6-P0.95-LS2.8-BL; MPN AP2112K-3.3TRG1; LCSC Part C51118
U21: SN65HVD230DR; SOIC-8_L4.9-W3.9-P1.27-LS6.0-BL; MPN SN65HVD230DR; LCSC Part C12084

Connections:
5V: C14.2, C76.2, D4.2 (K), J1.1, J5.1, J8.3, J8.4, R22.1, U10.5 (VCC), U20.1 (VIN), U20.3 (EN)
/CC1: R23.2, U1.A5 (CC1)
/CC2: R20.2, U1.B5 (CC2)
/DOUT: J1.2, U10.4 (Y)
/PROG_RX: J17.2, U19.40 (RXD0)
/PROG_TX: J17.3, U19.39 (TXD0)
CORE_CANH: J5.2, U21.7 (CANH)
CORE_CANL: J5.3, U21.6 (CANL)
CORE_CAN_RX: U19.8 (IO4), U21.4 (R)
CORE_CAN_TX: U19.9 (IO5), U21.1 (D)
GND: C14.1, C73.2, C74.1, C75.1, C76.1, C77.1, C78.2, D2.1 (K), D3.1 (K), J1.3, J5.5, J8.17, J8.18, J17.4, R20.1, R23.1, SW1.1, SW2.1, U1.1 (SHELL), U1.2 (SHELL), U1.3 (SHELL), U1.4 (SHELL), U1.A1B12 (GND), U1.B1A12 (GND), U10.3 (GND), U19.1 (GND), U19.2 (GND), U19.42 (GND), U19.43 (GND), U19.46 (GND), U19.47 (GND), U19.48 (GND), U19.49 (GND), U19.50 (GND), U19.51 (GND), U19.52 (GND), U19.53 (GND), U19.54 (GND), U19.55 (GND), U19.56 (GND), U19.57 (GND), U19.58 (GND), U19.59 (GND), U19.60 (GND), U19.61 (GND), U19.62 (GND), U19.63 (GND), U19.64 (GND), U19.65 (GND), U20.2 (GND), U21.2 (GND), U21.8 (RS); also elsewhere on the board
IO1: U19.5 (IO1)
IO2: U19.6 (IO2)
IO3: U19.7 (IO3)
IO6: U19.10 (IO6)
IO7: U19.11 (IO7)
IO8: U19.12 (IO8)
IO9: U19.13 (IO9)
IO10: U19.14 (IO10)
IO11: U19.15 (IO11)
IO12: U19.16 (IO12)
IO13: U19.17 (IO13)
IO14: U19.18 (IO14)
IO15: U19.19 (IO15)
IO16: U19.20 (IO16)
IO17: U19.21 (IO17)
IO18: U19.22 (IO18)
IO21: U19.25 (IO21)
IO26: U19.26 (IO26)
IO33: U19.28 (IO33)
IO35: J8.6, U19.31 (IO35)
IO36: J8.8, U19.32 (IO36)
IO37: J8.10, U19.33 (IO37)
IO38: J8.12, U19.34 (IO38)
IO39: J8.14, U19.35 (IO39)
IO40: J8.16, U19.36 (IO40)
IO41: J8.5, U19.37 (IO41)
IO42: J8.7, U19.38 (IO42)
IO45: J8.9, U19.41 (IO45)
IO46: J8.11, U19.44 (IO46)
IO47: J8.13, U19.27 (IO47)
IO48: J8.15, U19.30 (IO48)
LED_DATA: R10.1, U19.29 (IO34)
unnamed: D2.2 (A), R21.2
unnamed: D3.2 (A), R22.2
unnamed: R17.2, U1.A6 (D+), U1.B6 (D+)
unnamed: R18.2, U1.A7 (D-), U1.B7 (D-)
unnamed: R10.2, U10.2 (A)
unnamed: C73.1, R16.2, SW1.3, U19.45 (EN)
unnamed: R15.2, SW2.3, U19.4 (IO0)
TERM_CTRL_OUT: J5.4
USB_D+: R17.1, U19.24 (USB_D+)
USB_D-: R18.1, U19.23 (USB_D-)
VBUS: D4.1 (A), U1.A4B9 (VBUS), U1.B4A9 (VBUS)
VCORE: C74.2, C75.2, C77.2, C78.1, J8.1, J8.2, J17.1, R15.1, R16.1, R21.1, U19.3 (3V3), U20.5 (VOUT), U21.3 (VCC)

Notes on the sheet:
CAN TRANSCEIVER
CORE SUPPLY
CORE
LINK BAY
USB
LEDs
NB: INVERTING OUTPUT!!!
PROG
CONNECTORS
ARGB LED

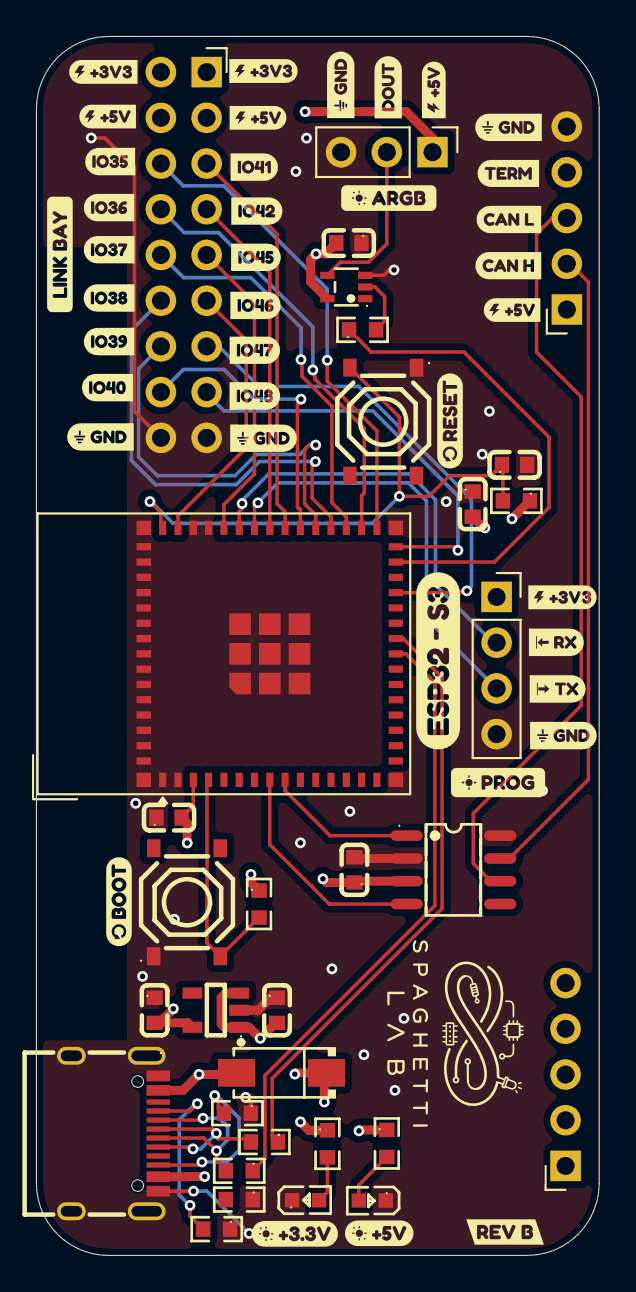
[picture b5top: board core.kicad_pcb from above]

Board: 4 copper layers, 31.3 x 67.7 mm, 71 parts (0 on the bottom side), 35 nets.

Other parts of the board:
R19: 5.1k; R0603
kobee-studio-6AA83E37, kobee-studio-6AA91FA3, kobee-studio-6AA91FB4, kobee-studio-6AA91FC0, kobee-studio-6AA91FC9, kobee-studio-6AA91FD2, kobee-studio-6AA924CD, kobee-studio-6AA9201C, kobee-studio-6AA9246B, kobee-studio-6AA9247D, kobee-studio-6AA9248F, kobee-studio-6AA9311E, kobee-studio-6AA9313B, kobee-studio-6AA9314C, kobee-studio-6AA9337A, kobee-studio-6AA91364, kobee-studio-6AA92015, kobee-studio-6AA92023, kobee-studio-6AA92029, kobee-studio-6AA92049, kobee-studio-6AA92476, kobee-studio-6AA92486, kobee-studio-6AA93134, kobee-studio-6AA93141, kobee-studio-6AA93147, kobee-studio-6AA93221, kobee-studio-6AABEAAD, kobee-studio-6AABEB0E, kobee-studio-6AABEB1D, kobee-studio-6AABEB02, kobee-studio-6AABEB2F, kobee-studio-6AABEB3C, kobee-studio-6AABEB18, kobee-studio-6AACD9C8, kobee-studio-6AACD9D1, kobee-studio-6AACD93B, kobee-studio-6AACD935, kobee-studio-6AACD940: Kobee Studio; kobee-studio-6AA83D3C
kobee-studio-6AA93394: Kobee Studio; kobee-studio-6AA91E6F

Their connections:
GND: R19.1; also elsewhere on the board
